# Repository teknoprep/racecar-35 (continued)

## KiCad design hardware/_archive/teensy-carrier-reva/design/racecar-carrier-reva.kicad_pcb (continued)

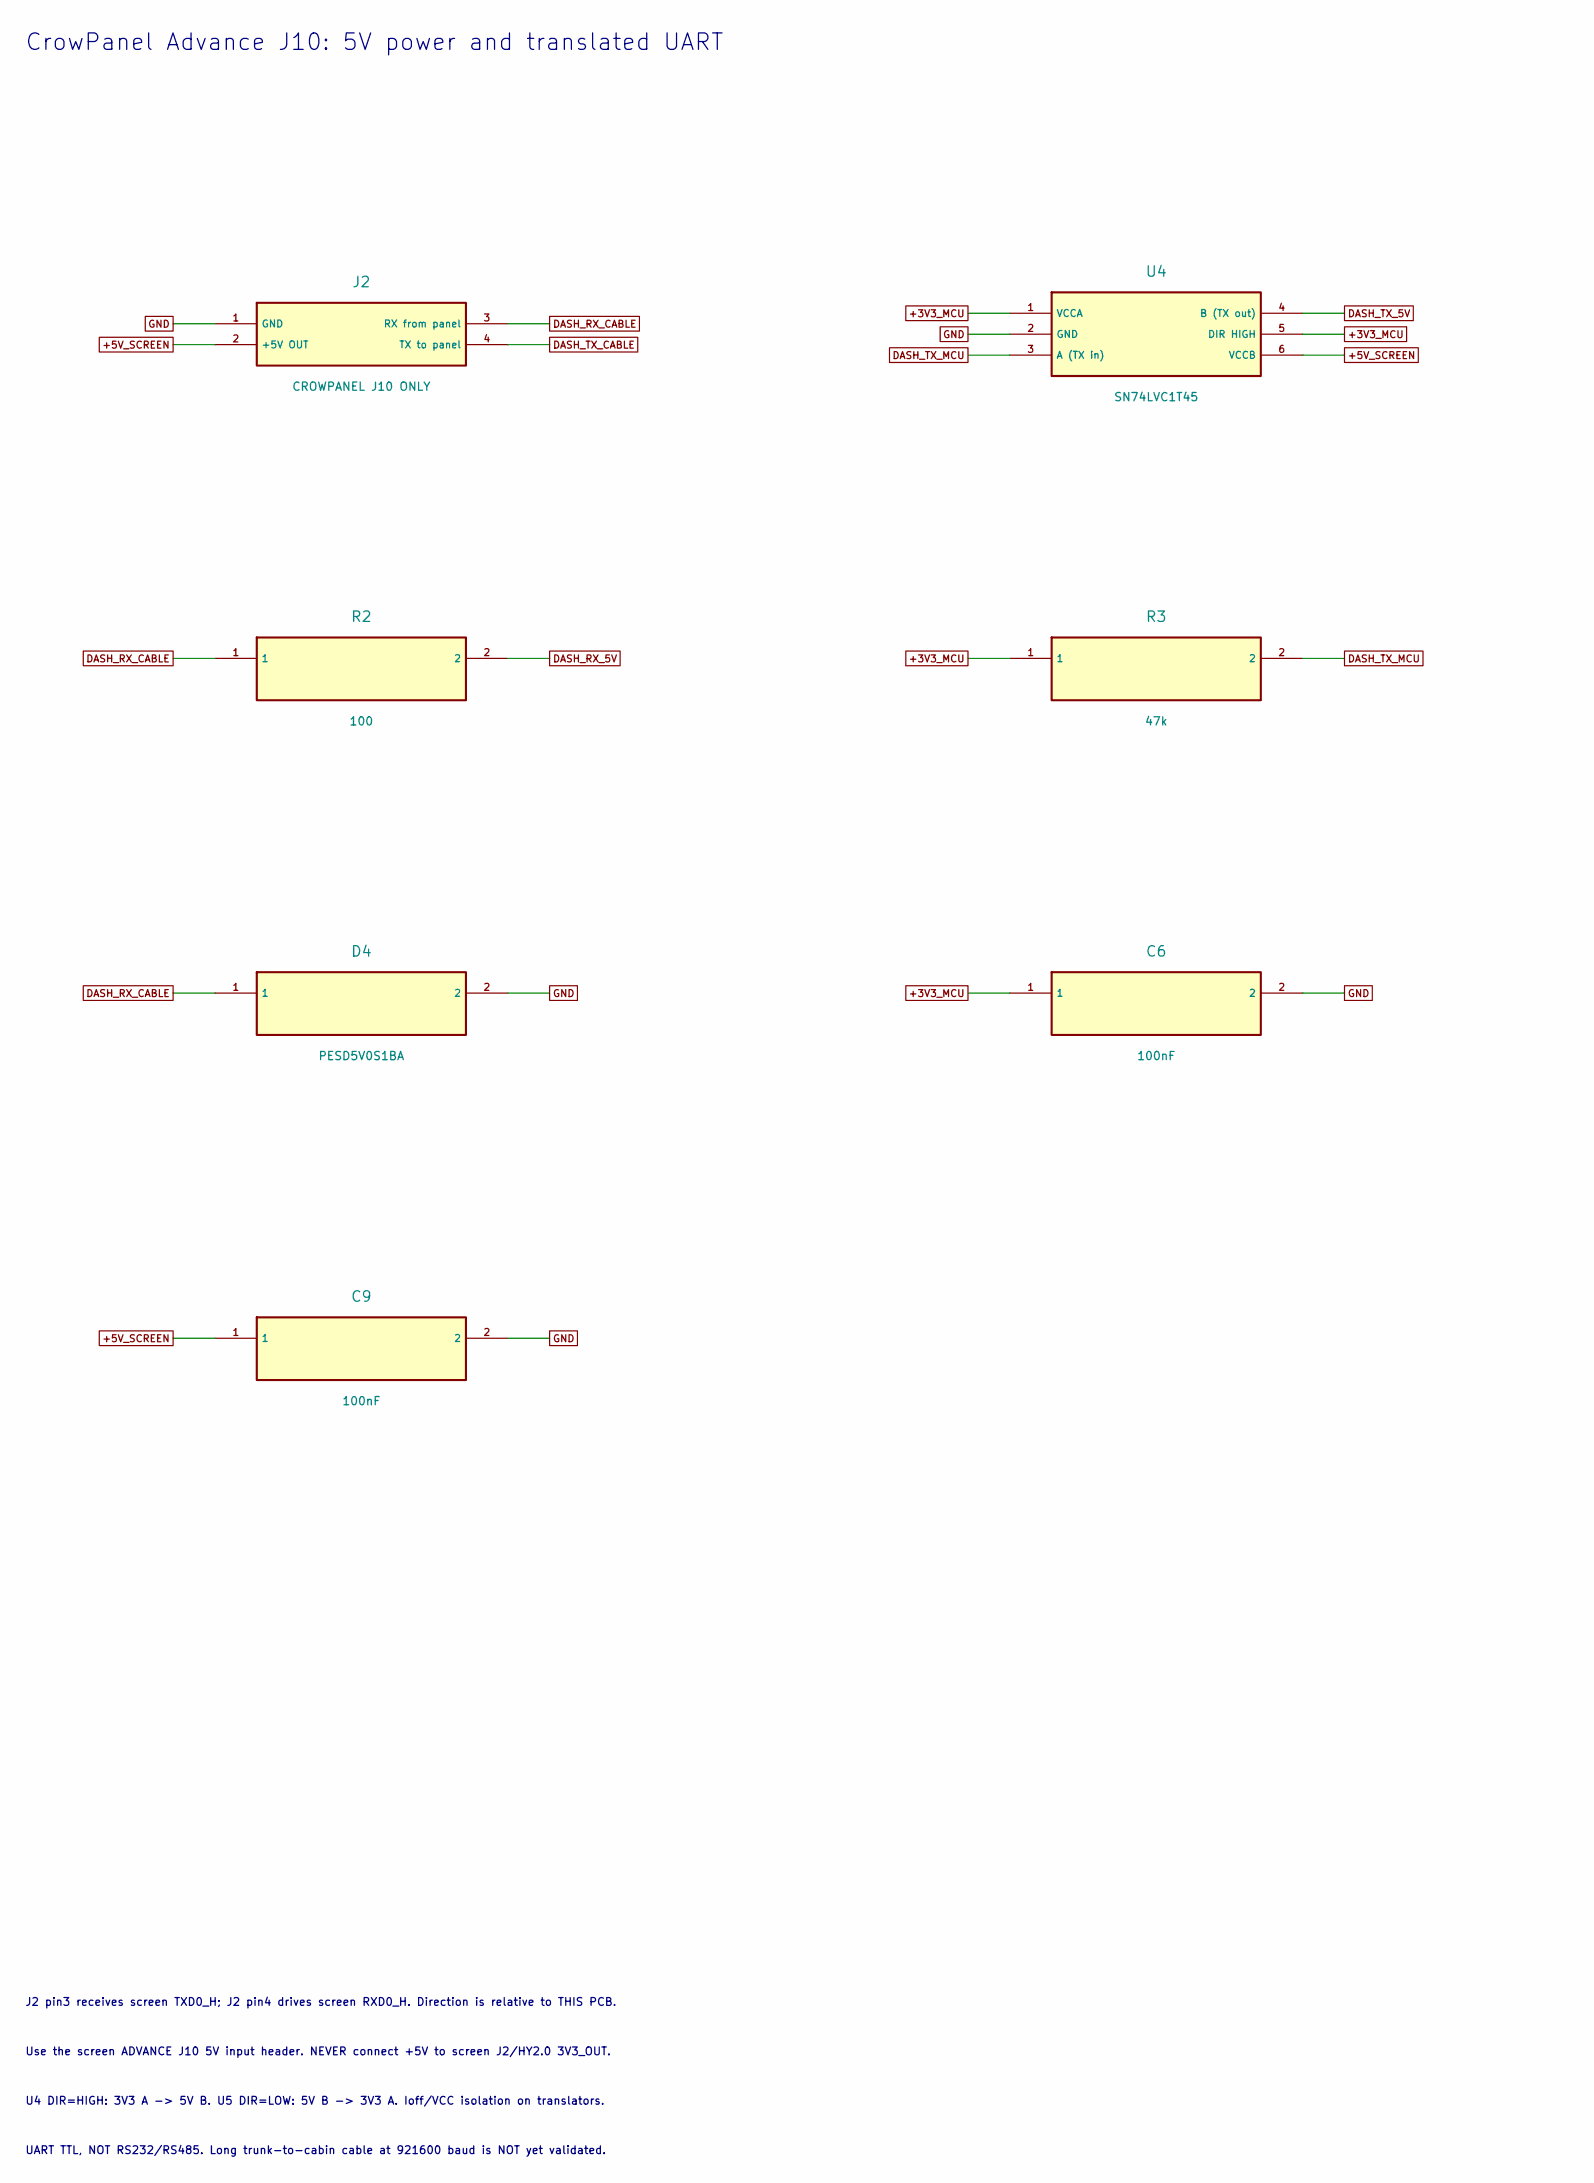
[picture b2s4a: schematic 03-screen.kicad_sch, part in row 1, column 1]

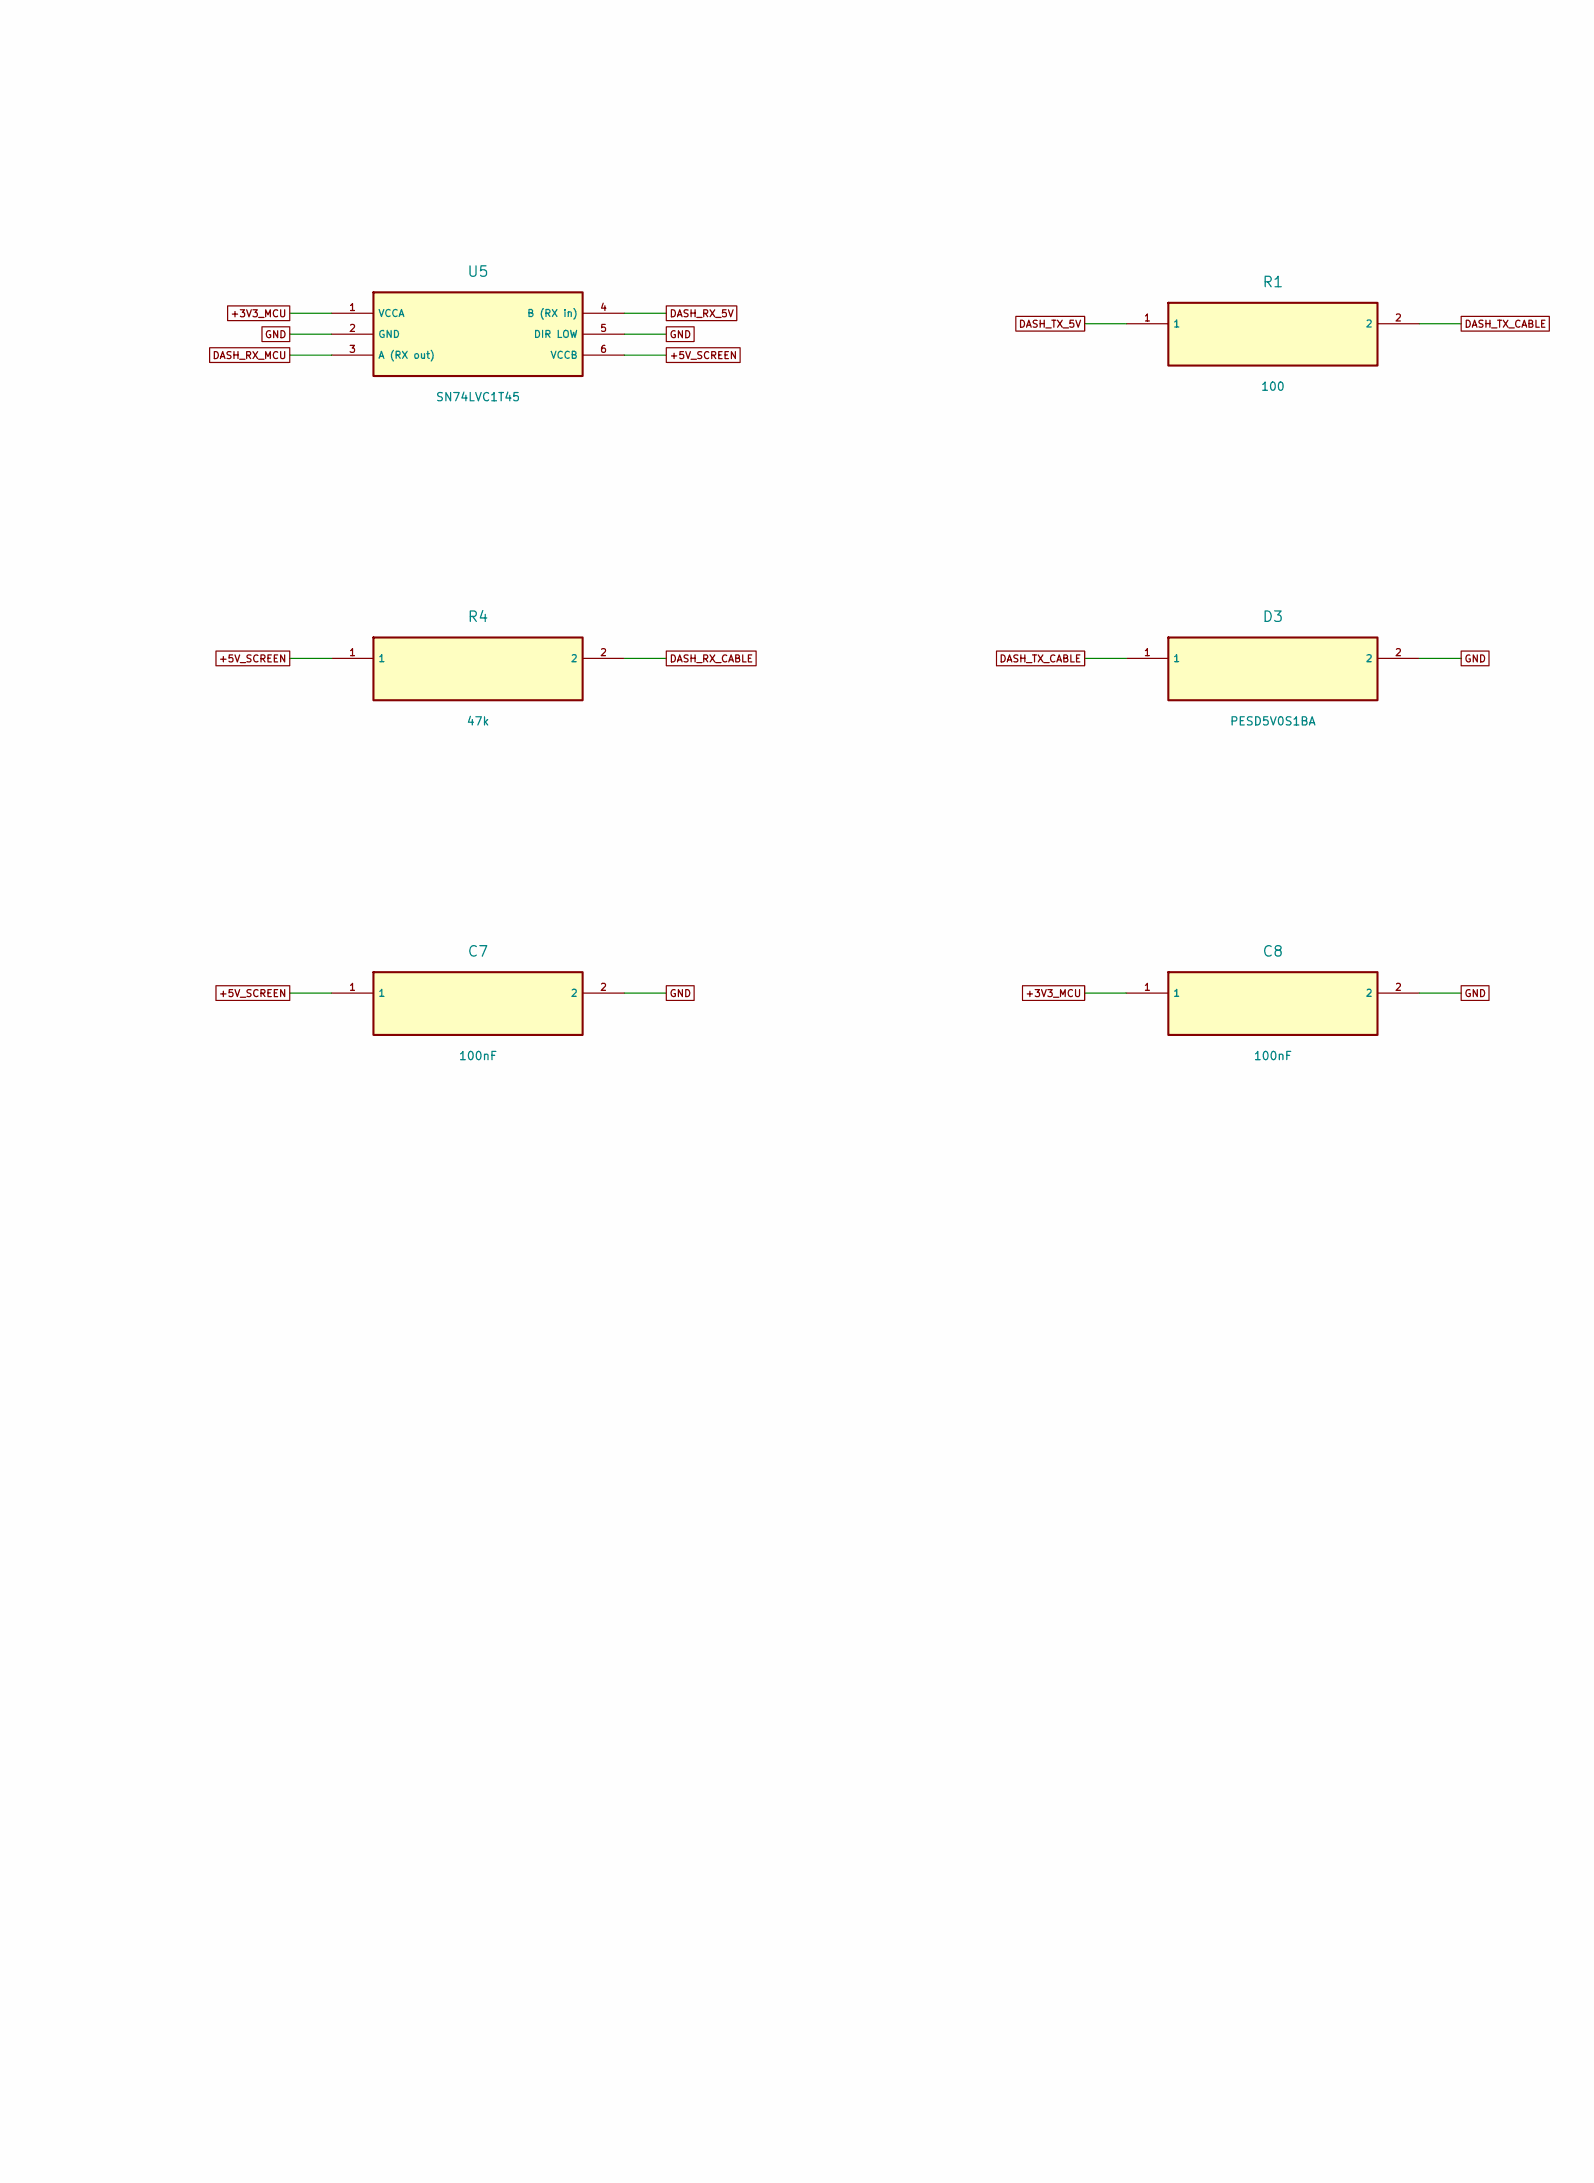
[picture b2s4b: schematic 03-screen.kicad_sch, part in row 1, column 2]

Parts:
C6, C7, C8, C9: 100nF; C_0805_2012Metric_Pad1.18x1.45mm_HandSolder
D3, D4: PESD5V0S1BA; D_SOD-323
J2: CROWPANEL J10 ONLY; TerminalBlock_Phoenix_MKDS-1,5-4-5.08_1x04_P5.08mm_Horizont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
R1, R2: 100; R_0805_2012Metric_Pad1.20x1.40mm_HandSolder
R3, R4: 47k; R_0805_2012Metric_Pad1.20x1.40mm_HandSolder
U4, U5: SN74LVC1T45; SOT-23-6_Handsoldering

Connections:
+3V3_MCU: C6.1, C8.1, R3.1, U4.1 (VCCA), U4.5 (DIR HIGH), U5.1 (VCCA); also elsewhere on the board
+5V_SCREEN: C7.1, C9.1, J2.2 (+5V OUT), R4.1, U4.6 (VCCB), U5.6 (VCCB); also elsewhere on the board
DASH_RX_5V: R2.2, U5.4 (B (RX in))
DASH_RX_CABLE: D4.1, J2.3 (RX from panel), R2.1, R4.2
DASH_RX_MCU: U5.3 (A (RX out)); also elsewhere on the board
DASH_TX_5V: R1.1, U4.4 (B (TX out))
DASH_TX_CABLE: D3.1, J2.4 (TX to panel), R1.2
DASH_TX_MCU: R3.2, U4.3 (A (TX in)); also elsewhere on the board
GND: C6.2, C7.2, C8.2, C9.2, D3.2, D4.2, J2.1 (GND), U4.2 (GND), U5.2 (GND), U5.5 (DIR LOW); also elsewhere on the board

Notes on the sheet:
CrowPanel Advance J10: 5V power and translated UART
J2 pin3 receives screen TXD0_H; J2 pin4 drives screen RXD0_H. Direction is relative to THIS PCB.
Use the screen ADVANCE J10 5V input header. NEVER connect +5V to screen J2/HY2.0 3V3_OUT.
U4 DIR=HIGH: 3V3 A -> 5V B. U5 DIR=LOW: 5V B -> 3V3 A. Ioff/VCC isolation on translators.
UART TTL, NOT RS232/RS485. Long trunk-to-cabin cable at 921600 baud is NOT yet validated.

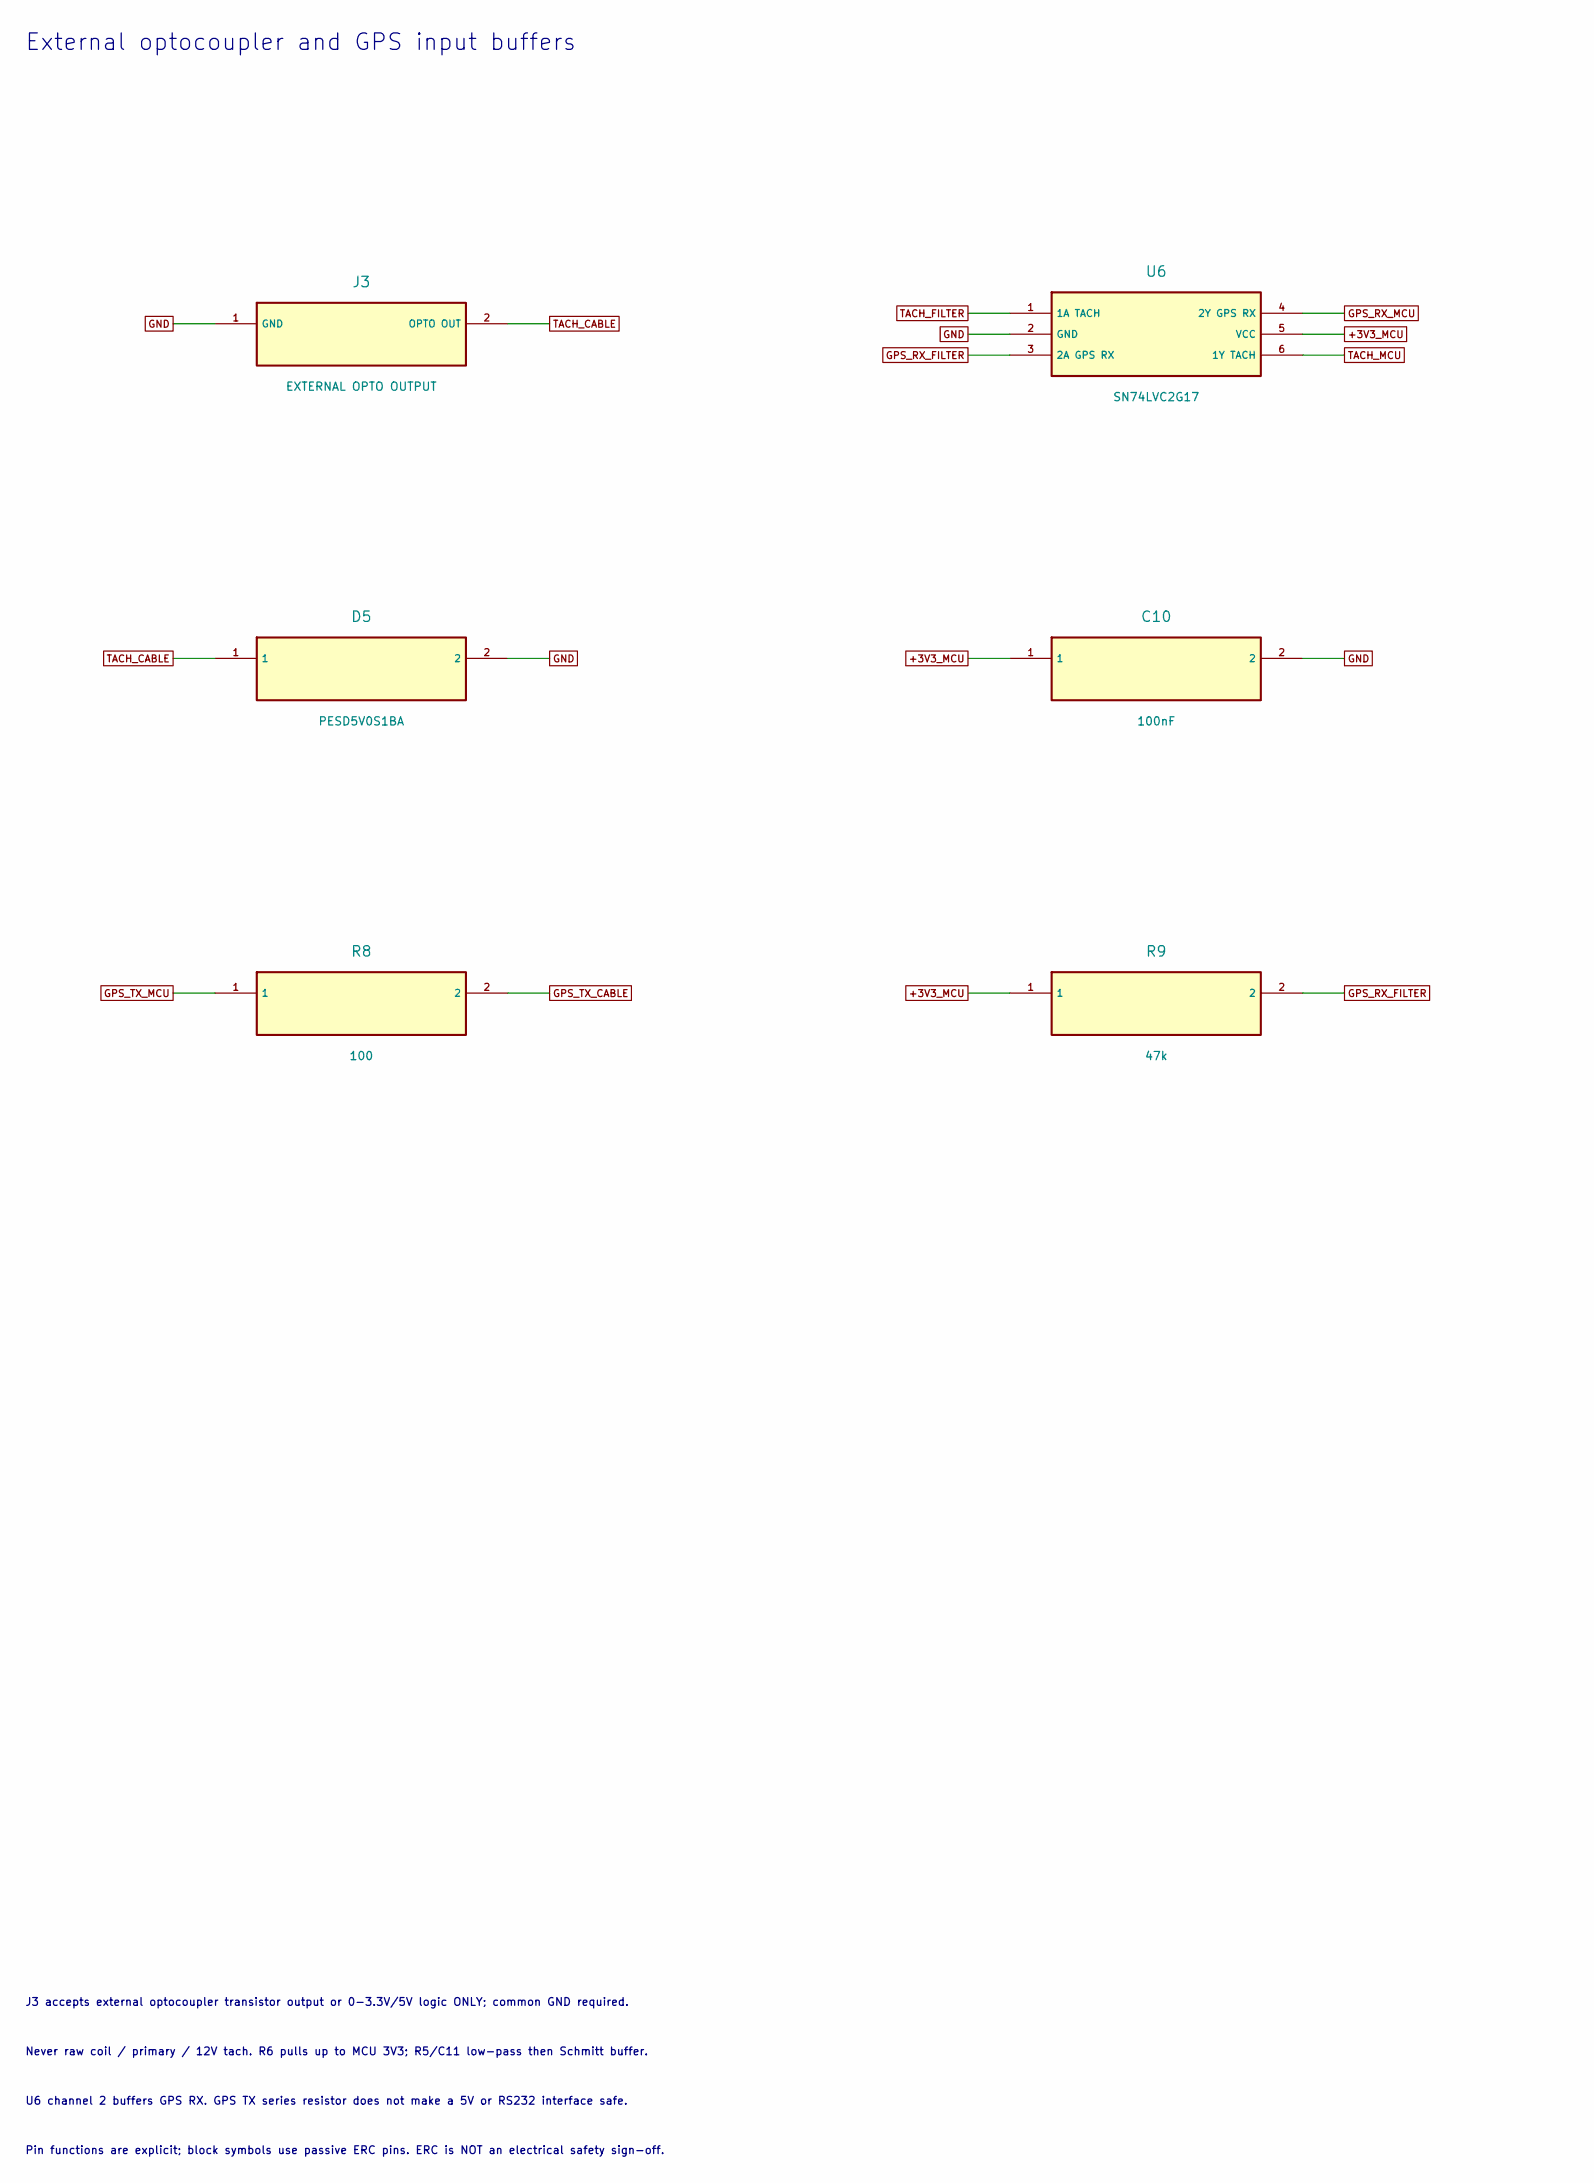
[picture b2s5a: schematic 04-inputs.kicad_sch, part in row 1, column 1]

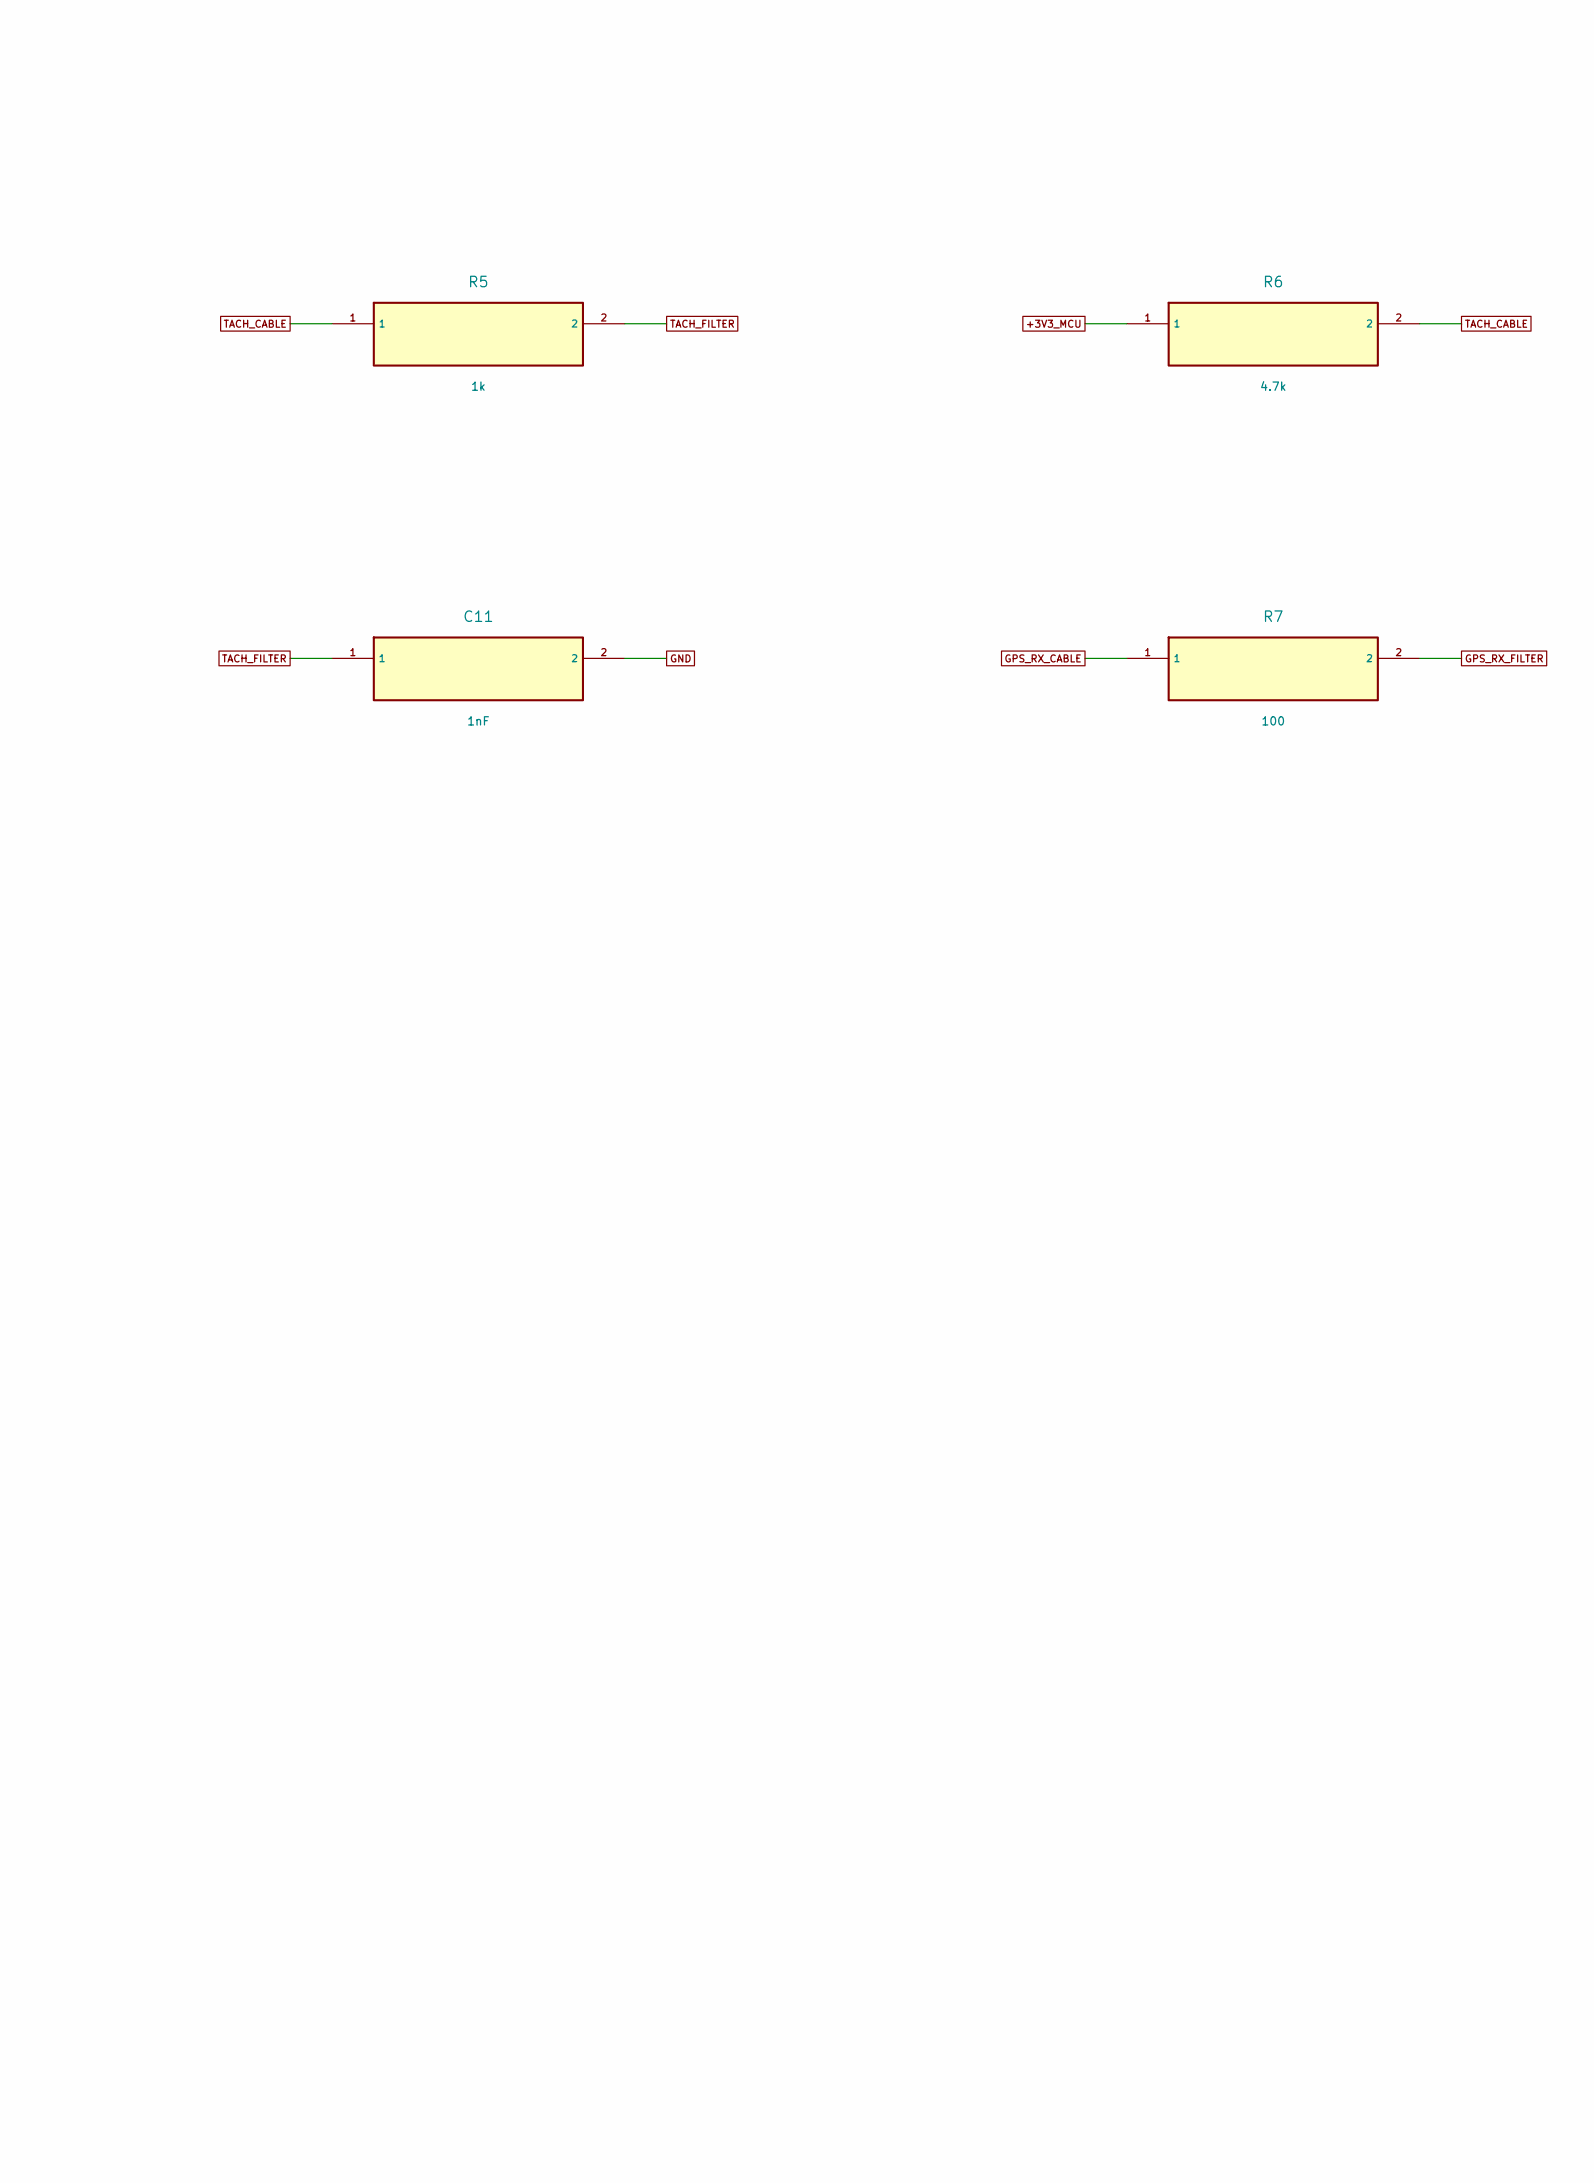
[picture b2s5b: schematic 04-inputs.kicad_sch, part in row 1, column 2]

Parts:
C10: 100nF; C_0805_2012Metric_Pad1.18x1.45mm_HandSolder
C11: 1nF; C_0805_2012Metric_Pad1.18x1.45mm_HandSolder
D5: PESD5V0S1BA; D_SOD-323
J3: EXTERNAL OPTO OUTPUT; TerminalBlock_Phoenix_MKDS-1,5-2-5.08_1x02_P5.08mm_Horizont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
R5: 1k; R_0805_2012Metric_Pad1.20x1.40mm_HandSolder
R6: 4.7k; R_0805_2012Metric_Pad1.20x1.40mm_HandSolder
R7, R8: 100; R_0805_2012Metric_Pad1.20x1.40mm_HandSolder
R9: 47k; R_0805_2012Metric_Pad1.20x1.40mm_HandSolder
U6: SN74LVC2G17; SOT-23-6_Handsoldering

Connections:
+3V3_MCU: C10.1, R6.1, R9.1, U6.5 (VCC); also elsewhere on the board
GND: C10.2, C11.2, D5.2, J3.1 (GND), U6.2 (GND); also elsewhere on the board
GPS_RX_CABLE: R7.1; also elsewhere on the board
GPS_RX_FILTER: R7.2, R9.2, U6.3 (2A GPS RX)
GPS_RX_MCU: U6.4 (2Y GPS RX); also elsewhere on the board
GPS_TX_CABLE: R8.2; also elsewhere on the board
GPS_TX_MCU: R8.1; also elsewhere on the board
TACH_CABLE: D5.1, J3.2 (OPTO OUT), R5.1, R6.2
TACH_FILTER: C11.1, R5.2, U6.1 (1A TACH)
TACH_MCU: U6.6 (1Y TACH); also elsewhere on the board

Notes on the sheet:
External optocoupler and GPS input buffers
J3 accepts external optocoupler transistor output or 0-3.3V/5V logic ONLY; common GND required.
Never raw coil / primary / 12V tach. R6 pulls up to MCU 3V3; R5/C11 low-pass then Schmitt buffer.
U6 channel 2 buffers GPS RX. GPS TX series resistor does not make a 5V or RS232 interface safe.
Pin functions are explicit; block symbols use passive ERC pins. ERC is NOT an electrical safety sign-off.

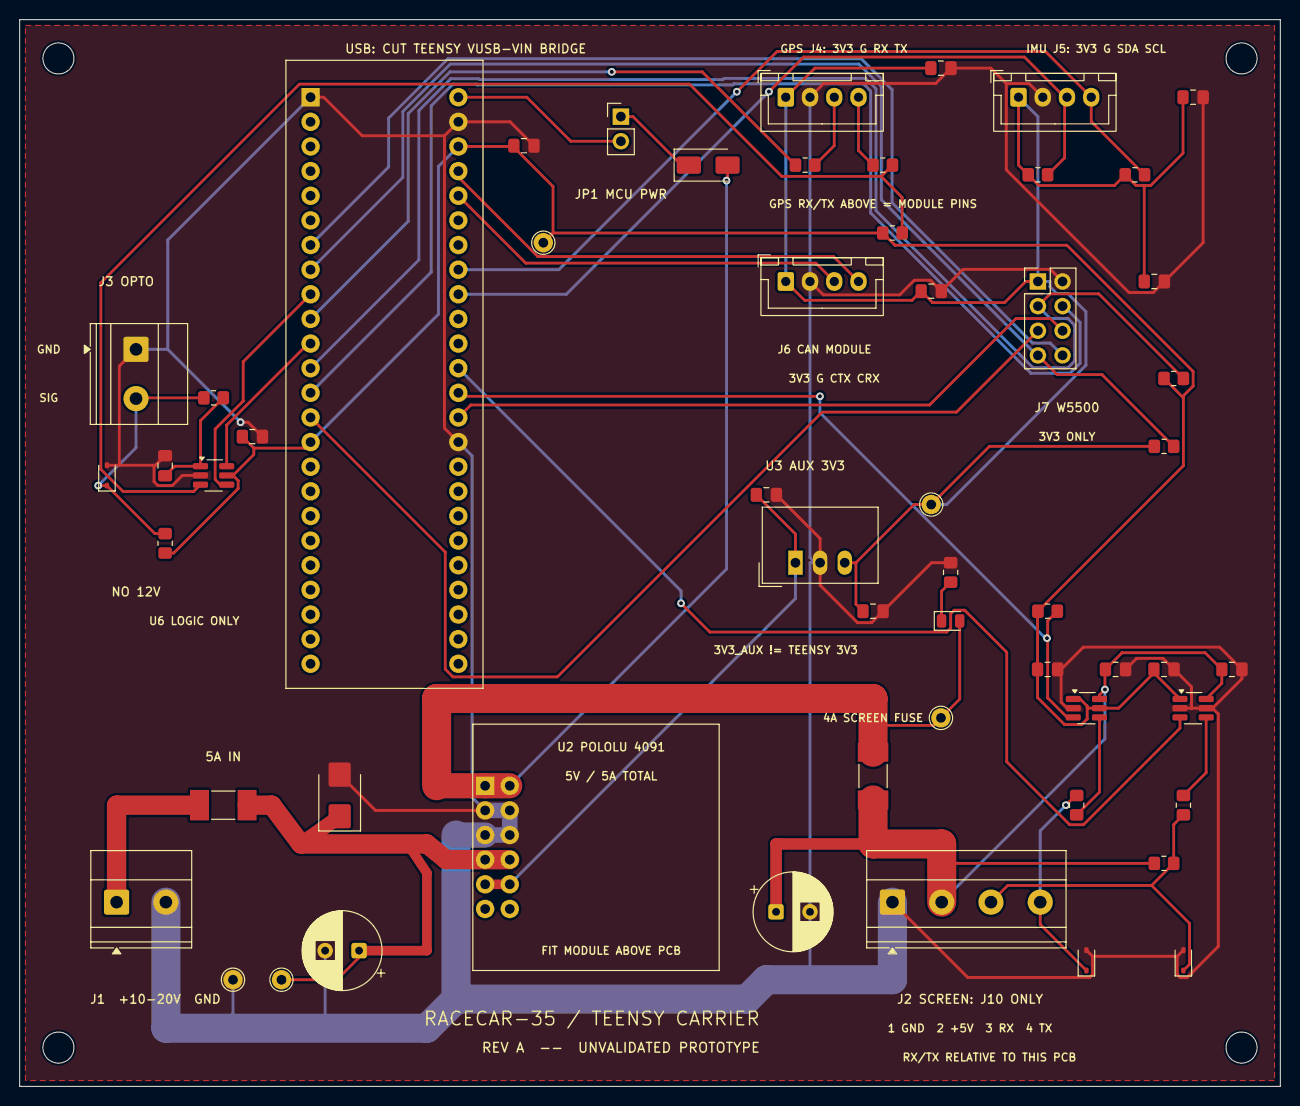
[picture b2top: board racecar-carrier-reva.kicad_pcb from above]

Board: 2 copper layers, 130.0 x 110.0 mm, 60 parts (0 on the bottom side), 35 nets.

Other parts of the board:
H1, H2, H3, H4: M3 MOUNT; MountingHole_3.2mm_M3

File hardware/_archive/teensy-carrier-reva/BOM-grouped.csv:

References,Quantity,Value,Manufacturer,MPN,Footprint
U1,1,Teensy 4.1 (socketed),PJRC,TEENSY41,Racecar:Teensy41_Socket
U2,1,D36V50F5 / 5V 5A budget,Pololu,4091 / D36V50F5,Racecar:Pololu_D36V50F5
U3,1,TSR 1-2433 / AUX 3V3,Traco Power,TSR 1-2433,Racecar:Converter_DCDC_TRACO_TSR-1_THT
J1,1,10-20V INPUT,Phoenix Contact,1729018,"Racecar:TerminalBlock_Phoenix_MKDS-1,5-2-5.08_1x02_P5.08mm_Horizontal"
J2,1,CROWPANEL J10 ONLY,Phoenix Contact,1729034,"Racecar:TerminalBlock_Phoenix_MKDS-1,5-4-5.08_1x04_P5.08mm_Horizontal"
J3,1,EXTERNAL OPTO OUTPUT,Phoenix Contact,1729018,"Racecar:TerminalBlock_Phoenix_MKDS-1,5-2-5.08_1x02_P5.08mm_Horizontal"
J4,1,GPS UART 3V3,JST,B4B-XH-A(LF)(SN),Racecar:JST_XH_B4B-XH-A_1x04_P2.50mm_Vertical
J5,1,MPU6050 I2C 3V3,JST,B4B-XH-A(LF)(SN),Racecar:JST_XH_B4B-XH-A_1x04_P2.50mm_Vertical
J6,1,CAN MODULE LOGIC,JST,B4B-XH-A(LF)(SN),Racecar:JST_XH_B4B-XH-A_1x04_P2.50mm_Vertical
J7,1,W5500 BREAKOUT,Samtec,TSW-104-07-G-D,Racecar:PinHeader_2x04_P2.54mm_Vertical
JP1,1,MCU POWER ENABLE,Samtec,TSW-102-07-G-S,Racecar:PinHeader_1x02_P2.54mm_Vertical
D2,1,SS14 USB backfeed barrier,Diodes Inc.,SS14,Racecar:D_SMA
F1,1,5A INPUT FUSE,Littelfuse,0451005.MRL,Racecar:Fuse_Littelfuse-NANO2-451_453
F2,1,4A SCREEN FUSE,Littelfuse,0451004.MRL,Racecar:Fuse_Littelfuse-NANO2-451_453
D1,1,SMBJ20CA INPUT TVS,Littelfuse,SMBJ20CA,Racecar:D_SMB
C1,1,100uF 50V,Panasonic,EEU-FR1H101,Racecar:CP_Radial_D8.0mm_P3.50mm
C2,1,470uF 10V,Panasonic,EEU-FR1A471B,Racecar:CP_Radial_D8.0mm_P3.50mm
"C3, C4, C5, C6, C7, C8, C9, C10, C12, C13, C14, C15",12,100nF,Murata,GRM21BR71H104KA01L,Racecar:C_0805_2012Metric_Pad1.18x1.45mm_HandSolder
"U4, U5",2,SN74LVC1T45,Texas Instruments,SN74LVC1T45DBVR,Racecar:SOT-23-6_Handsoldering
"R1, R2, R7, R8",4,100,Yageo,RC0805FR-07100RL,Racecar:R_0805_2012Metric_Pad1.20x1.40mm_HandSolder
"R3, R4, R9",3,47k,Yageo,RC0805FR-0747KL,Racecar:R_0805_2012Metric_Pad1.20x1.40mm_HandSolder
"D3, D4, D5",3,PESD5V0S1BA,Nexperia,"PESD5V0S1BA,115",Racecar:D_SOD-323
U6,1,SN74LVC2G17,Texas Instruments,SN74LVC2G17DBVR,Racecar:SOT-23-6_Handsoldering
C11,1,1nF,Murata,GRM21BR71H102KA01L,Racecar:C_0805_2012Metric_Pad1.18x1.45mm_HandSolder
R5,1,1k,Yageo,RC0805FR-071KL,Racecar:R_0805_2012Metric_Pad1.20x1.40mm_HandSolder
"R6, R12, R13, R14",4,4.7k,Yageo,RC0805FR-074K7L,Racecar:R_0805_2012Metric_Pad1.20x1.40mm_HandSolder
"R10, R11",2,10k,Yageo,RC0805FR-0710KL,Racecar:R_0805_2012Metric_Pad1.20x1.40mm_HandSolder
D6,1,GREEN 5V,Lite-On,LTST-C170KGKT,Racecar:LED_0805_2012Metric
